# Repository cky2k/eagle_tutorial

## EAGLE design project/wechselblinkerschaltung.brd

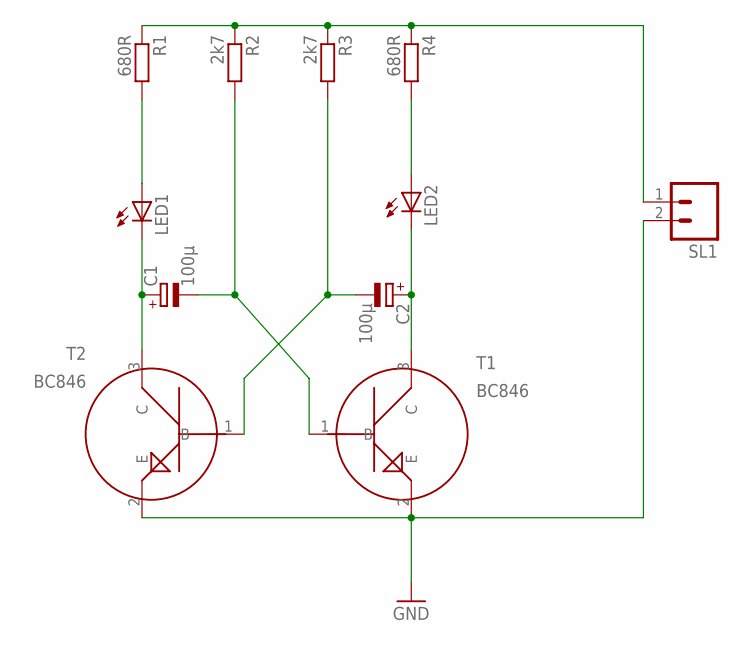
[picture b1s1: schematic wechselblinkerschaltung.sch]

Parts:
C1, C2: 100µ; E2,5-6
LED1, LED2: LED5MM
R1, R4: 680R; R0805
R2, R3: 2k7; R0805
SL1: M02; 02P
T1, T2: BC846; SOT23

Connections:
GND: SL1.2, T1.2 (E), T2.2 (E)
unnamed: R1.1, R2.1, R3.1, R4.1, SL1.1
unnamed: LED1.A, R1.2
unnamed: C1.+, LED1.K (C), T2.3 (C)
unnamed: LED2.A, R4.2
unnamed: C2.+, LED2.K (C), T1.3 (C)
unnamed: C2.-, R3.2, T2.1 (B)
unnamed: C1.-, R2.2, T1.1 (B)

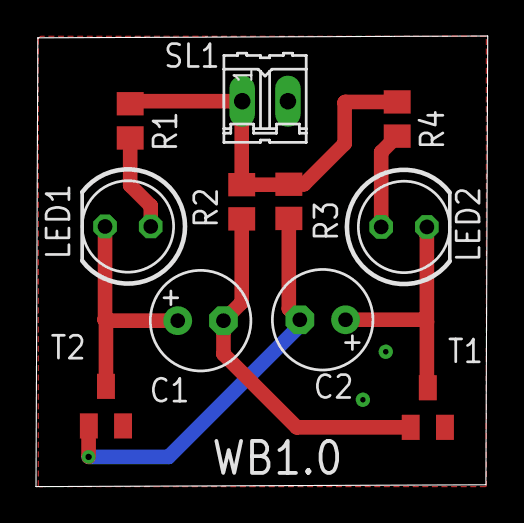
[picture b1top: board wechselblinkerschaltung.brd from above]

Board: 2 copper layers, 25.1 x 25.0 mm, 11 parts (0 on the bottom side), 8 nets.

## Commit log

2019-02-13 Library von Tutorial Teil 2.
2019-03-06 Tutorial Teil3 und Teil4 files hinzugefügt.
2019-03-08 Tutorial Teil 5 Gerberdaten
